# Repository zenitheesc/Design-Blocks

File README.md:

<h1 align="center" style="color:white; background-color:black">Design blocks</h1>
<h4 align="center">Collection of circuits and Documentation</h4>

<p align="center">

</p>

<p align="center">
    <a href="#Objective">Objective</a> •
    <a href="#Enviroment">Enviroment</a> •
    <a href="#Adding-a-Design-Block">Adding a Design Block</a>
</p>

## Objective

Unify all circuits designed by the group adding proper documentation.

## Environment

Our circuits are mainly developed in [KiCad](https://www.kicad.org/).

## Adding a Design Block

1. Clone this repository
 2. Create a folder with the Circuit name
 3. Add the appropriate files according to the software used 
 4. Add a `README.md` file to the Driver folder 
    1. On the README add the Author, Date, and purpose of the library
    2. Add Documentation: Schematic, Layout and B.O.M. 
    3. Add a notes section for any extra information on circuit usage and performance
 5. Add a folder called `Docs`
    1. Add any External Documentation including Datasheets, Application Notes, and Register Maps
 6. If there is a GitHub Issue for the Design Blocks add a message or close it.

---

<p align="center">

</p>
<p align = "center">
<a href="zenith.eesc@gmail.com">zenith.eesc@gmail.com</a>
</p>

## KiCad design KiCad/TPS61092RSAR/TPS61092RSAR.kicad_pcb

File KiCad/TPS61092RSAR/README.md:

# TPS61092RSAR

DC-DC Step-Up Converter from 3.6V to 5V (2A Current), developed to be used in the Ground Station Mobile "Alcântara".

# Schematic

# Layout

# Tests

## Validation

Circuit awaiting manufacture.

# B.O.M.
|Component|Amount|Description|
|--|--|--|
|TPS61092RSAR|1|Conversor Boost|
|Inductor|1|6.8 uH SMD|
|Capacitor|1|10 uF SMD 0805|
|Capacitor|1|2.2 uF SMD 0805|
|Capacitor|1|100 uF SMD Low ESR Tantalum|
|Resistor|1|2.7 Mohm SMD 0805|
|Resistor|1|390 kohm SMD 0805|
|Resistor|1|1 Mohm SMD 0805|

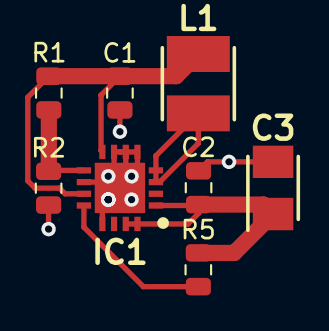
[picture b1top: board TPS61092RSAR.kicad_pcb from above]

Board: 2 copper layers, 8 parts (0 on the bottom side), 6 nets.

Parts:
C1: 10u; C_0805_2012Metric
C2: 2.2u; C_0805_2012Metric
C3: 100u; CAPPM3528X210N
IC1: TPS61092RSAR; QFN65P400X400X100-17N
L1: 6.8u; INDPM4040X210N
R1: 2.7M; R_0805_2012Metric
R2: 390k; R_0805_2012Metric
R5: 1M; R_0805_2012Metric

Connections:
+5V: C2.1, C3.1, IC1.1, IC1.15, IC1.16, R5.1
/Pack: C1.1, IC1.8, IC1.11, L1.1, R1.1
GND: C1.2, C2.2, C3.2, IC1.5, IC1.6, IC1.7, IC1.10, IC1.13, IC1.17, R2.2
unnamed: IC1.3, IC1.4, L1.2
unnamed: IC1.9, R1.2, R2.1
unnamed: IC1.12, R5.2

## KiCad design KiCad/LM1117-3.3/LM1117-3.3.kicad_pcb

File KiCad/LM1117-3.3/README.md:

# LM1117-3.3

Linear regulator from 5V to 3.3V (current of 0.8A), developed to be used in Ground Station Mobile "Alcântara".

# Schematic

# Layout

# Tests

## Validation

Circuit awaiting manufacture.

# B.O.M.
|Component|Amount|Description|
|--|--|--|
|LM1117-3.3|1|3.3V Voltage Regulator 800-mA|
|Capacitor|2|10 uF SMD 1206 Tantalum|

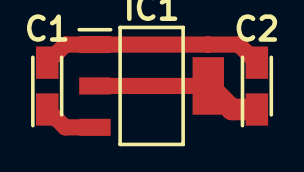
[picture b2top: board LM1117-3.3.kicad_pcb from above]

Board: 2 copper layers, 3 parts (0 on the bottom side), 3 nets.

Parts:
C1, C2: 10u; CAPPM3216X180N
IC1: LM1117MPX-3.3; SOT230P700X180-4N

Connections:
+3V3: C2.1, IC1.2, IC1.4
/Pack: C1.1, IC1.3
GND: C1.2, C2.2, IC1.1

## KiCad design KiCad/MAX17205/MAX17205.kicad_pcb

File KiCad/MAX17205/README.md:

# Max17205

Circuit for monitoring the state of charge of a lithium ion cell (18650), developed to be used in the ground station mobile "Alcântara".

# Schematic

# Layout

## Validation

Circuit awaiting manufacture.

# B.O.M.
|Component|Amount|Description|
|--|--|--|
|MAX17205G+T|1|S.O.C. Monitor|
|Holder|1|18650 Holder|
|Thermistor|1|NTC 10 kohm SMD 0402|
|Shunt Resistor|1|10 mohm, 1 W 0805 SMD|
|Resistor|1|10 ohm SMD 0805|
|Resistor|1|10 kohm SMD 0805|
|Resistor|3|4.7 kohm SMD 0805|
|Capacitor|1|100 pF SMD 0805|
|Capacitor|1|470 pF SMD 0805|

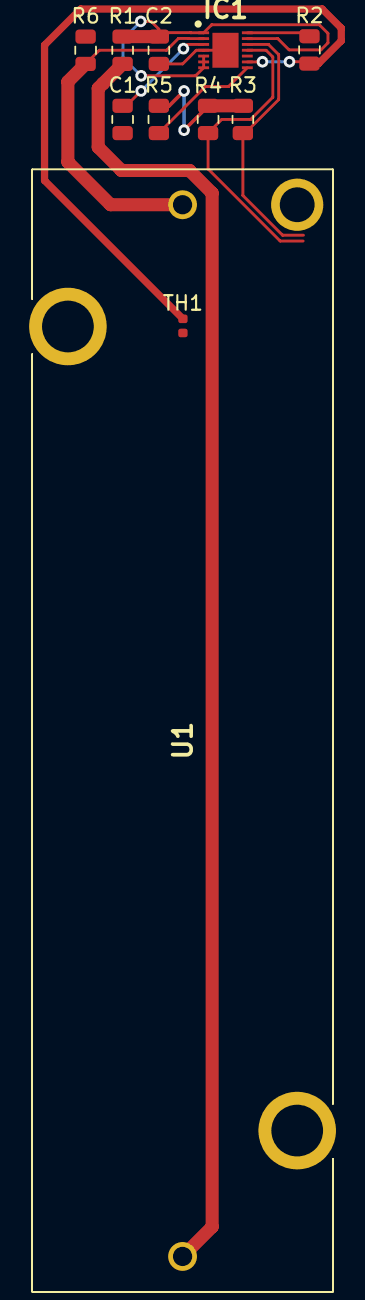
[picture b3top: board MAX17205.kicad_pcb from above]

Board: 2 copper layers, 11 parts (0 on the bottom side), 11 nets.

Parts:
C1: 470p; C_0805_2012Metric
C2: 100p; C_0805_2012Metric
IC1: MAX17205G+T; SON40P300X300X80-15N
R1: 10; R_0805_2012Metric
R2: 10k; R_0805_2012Metric
R3, R4, R5: 4.7k; R_0805_2012Metric
R6: 10m; R_0805_2012Metric
TH1: 10k; R_0402_1005Metric
U1: 1043

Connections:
+3V3: R3.1, R4.1, R5.1
/ALRT1: IC1.8, R5.2
/Pack: R1.2, U1.1
/SCL: IC1.11, R4.2
/SDA: IC1.12, R3.2
GND: C1.2, C2.2, IC1.4, IC1.15, R6.2, TH1.2
unnamed: C1.1, IC1.3
unnamed: C2.1, IC1.1, IC1.5, IC1.6, IC1.7, IC1.13, R1.1
unnamed: IC1.2, R6.1, U1.2
unnamed: IC1.9, R2.1, TH1.1
unnamed: IC1.14, R2.2

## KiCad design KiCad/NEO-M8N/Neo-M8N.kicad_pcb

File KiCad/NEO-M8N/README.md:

# NEO-M8N

GNSS ublox, developed to be used in probe launches.

# Schematic

# Layout

# Tests

## Validation

Circuit awaiting manufacture.

# B.O.M.
|Component|Amount|Description|
|--|--|--|
|NEO-M8N|1|GNSS|
|SMA|1|RF Connector SMD|
|Capacitor|1|100 nF SMD 0805|
|Resistor|2|4.7 kohm SMD 0805|

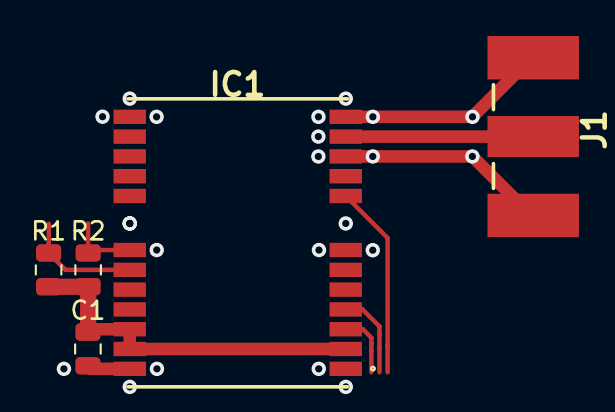
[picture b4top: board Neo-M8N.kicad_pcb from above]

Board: 2 copper layers, 5 parts (0 on the bottom side), 5 nets.

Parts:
C1: 100n; C_0805_2012Metric
IC1: NEO-M8N-0; NEO-M8T
J1: 142-0701-801; 142-0701-851
R1, R2: 4.7k; R_0805_2012Metric

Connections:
+3V3: C1.1, IC1.2, IC1.22, IC1.23, R1.1, R2.1
/SCL: IC1.19, R1.2
/SDA: IC1.18, R2.2
GND: C1.2, IC1.7, IC1.10, IC1.12, IC1.13, IC1.24, J1.1, J1.3
unnamed: IC1.11, J1.2

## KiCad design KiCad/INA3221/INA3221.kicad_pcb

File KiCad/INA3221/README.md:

# INA3221

Circuit capable of monitoring voltage and current through three different channels and communicating measurements via I2C.

# Schematic

# Layout

# Tests
## Validation

[Descrever testes quando o circuito for manufaturado]

# Addressing
Connect only one solder jumper at a time to set the I2C device address.
|A0|Address|
|--|--|
|GND|1000000|
|VCC|1000001|
|SDA|1000010|
|SCL|1000011|

# B.O.M.
|Component|Amount|Description|
|--|--|--|
|INA3221|1|Three-channel I2C current monitor|
|Shunt resistor|3|2.8 ohm, 1 W 2512 SMD resistor|
|Resisor|6|10kohm SMD 0805 resistor|
|Capacitor|1|100nF SMD capacitor 0805|

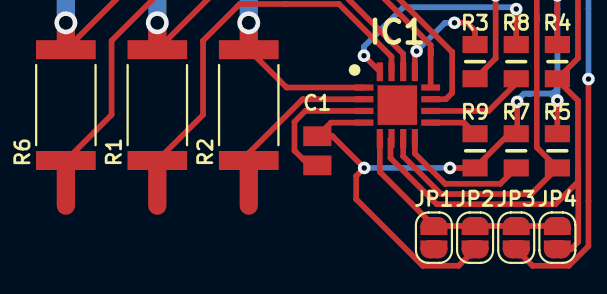
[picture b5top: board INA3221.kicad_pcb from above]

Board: 2 copper layers, 15 parts (0 on the bottom side), 16 nets.

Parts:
C1: 0,1u; CAPC2012X100N
IC1: INA3221; QFN65P400X400X100-17N-D
JP1, JP2, JP3, JP4: SolderJumper_2_Open; SolderJumper-2_P1.3mm_Open_RoundedPad1.0x1.5mm
R1, R2, R6: 2,8; RESC6432X70N
R3, R4, R5, R7, R8, R9: 10k; RESC2012X60N

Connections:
/+3V3: C1.1, IC1.4, JP2.1, R3.1, R4.1, R5.1, R7.1, R9.1
/Critical: IC1.9, R9.2
/GND: C1.2, IC1.3, JP1.1
/IN1+: IC1.12, R6.2
/IN1-: IC1.11, R6.1
/IN2+: IC1.15, R1.1
/IN2-: IC1.14, R1.2
/IN3+: IC1.2, R2.1
/IN3-: IC1.1, R2.2
/PV: IC1.10, R8.2
/SCL: IC1.6, JP4.1, R4.2
/SDA: IC1.7, JP3.1, R5.2
/TC: IC1.13, R3.2
/VPU: IC1.16, R8.1
/Warning: IC1.8, R7.2
unnamed: IC1.5, JP1.2, JP2.2, JP3.2, JP4.2

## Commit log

2020-08-27 Create Micro_SD
